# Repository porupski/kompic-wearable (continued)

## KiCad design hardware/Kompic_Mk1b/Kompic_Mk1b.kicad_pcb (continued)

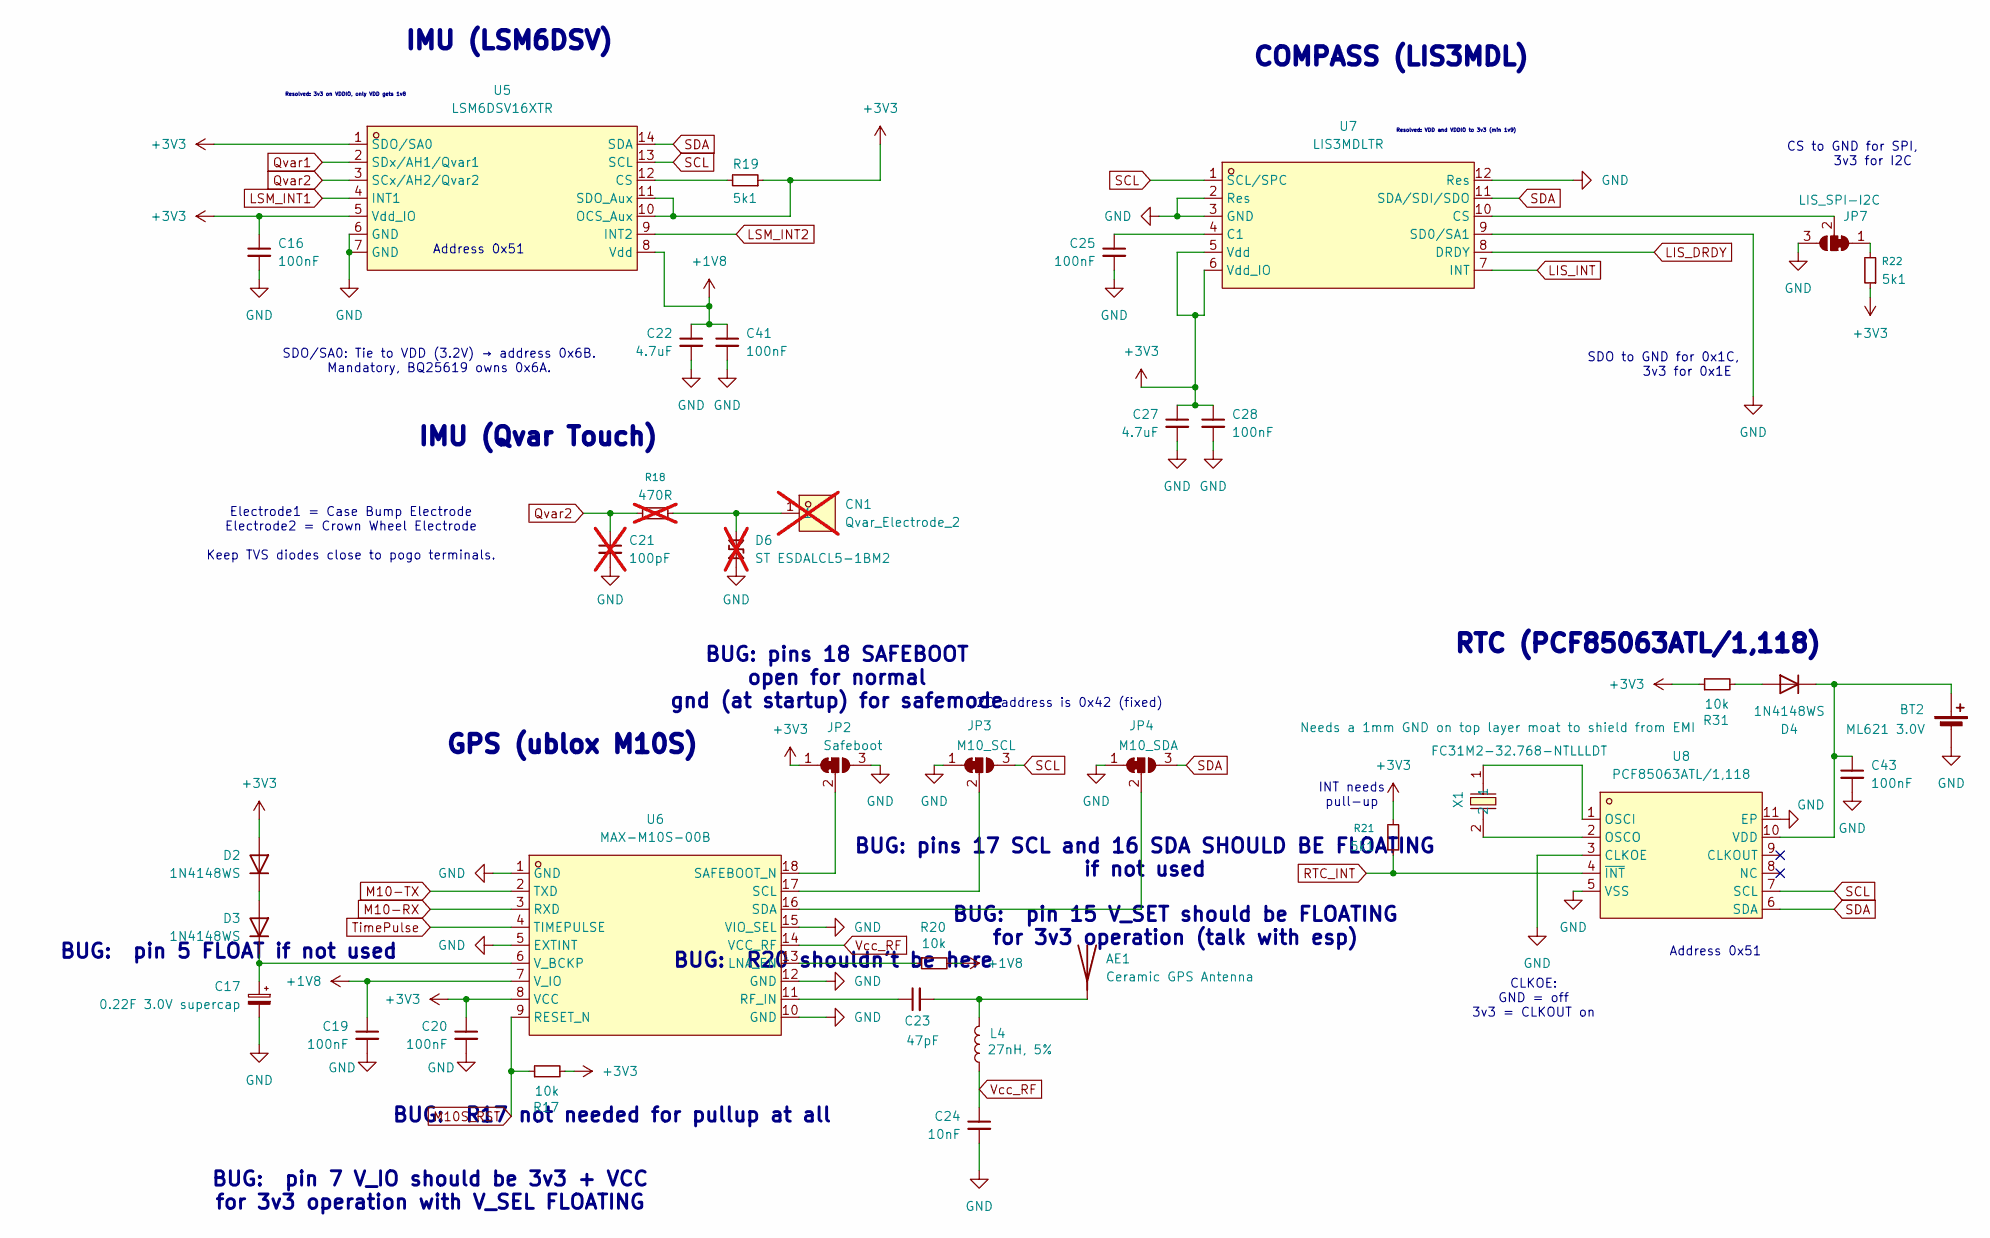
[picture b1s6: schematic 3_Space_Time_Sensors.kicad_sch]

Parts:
AE1: Ceramic GPS Antenna; GPS_Ceramic_Antenna_8x8mm_v1.0
BT2: ML621 3.0V; DMS_3R3_224_supercap_feets_v1
C16, C19, C20, C25, C28, C41, C43: 100nF; C_0402_1005Metric_Pad0.74x0.62mm_HandSolder
C17: 0.22F 3.0V supercap; DMS_3R3_224_supercap_feets_v1
C21: 100pF; C_0402_1005Metric_Pad0.74x0.62mm_HandSolder; not fitted
C22, C27: 4.7uF; C_0402_1005Metric_Pad0.74x0.62mm_HandSolder
C23: 47pF; C_0402_1005Metric_Pad0.74x0.62mm_HandSolder
C24: 10nF; C_0402_1005Metric_Pad0.74x0.62mm_HandSolder
CN1: Qvar_Electrode_2; TestPoint_Pad_D1.5mm; MPN YZR0028-15020-01; LCSC Part C7429439; not fitted
D2, D3, D4: 1N4148WS; D_SOD-323
D6: ST ESDALCL5-1BM2; D_SOD-882; not fitted
JP2: Safeboot; SolderJumper-3_P1.3mm_Bridged2Bar12_RoundedPad1.0x1.5mm
JP3: M10_SCL; SolderJumper-3_P1.3mm_Bridged2Bar12_RoundedPad1.0x1.5mm
JP4: M10_SDA; SolderJumper-3_P1.3mm_Bridged2Bar12_RoundedPad1.0x1.5mm
JP7: LIS_SPI-I2C; SolderJumper-3_P1.3mm_Bridged2Bar12_RoundedPad1.0x1.5mm
L4: 27nH, 5%; C_0402_1005Metric_Pad0.74x0.62mm_HandSolder
R17, R20, R31: 10k; R_0402_1005Metric_Pad0.72x0.64mm_HandSolder
R18: 470R; R_0402_1005Metric_Pad0.72x0.64mm_HandSolder; not fitted
R19, R21, R22: 5k1; R_0402_1005Metric_Pad0.72x0.64mm_HandSolder
U5: LSM6DSV16XTR; LGA-14_L3.0-W2.5-P0.50-BR; LCSC Part C5267406
U6: MAX-M10S-00B; SMD-18_L10.1-W9.7-P1.10-TL_SKG09F; LCSC Part C4153167
U7: LIS3MDLTR; LGA-12_L2.0-W2.0-P0.50-BL; LCSC Part C478483
U8: PCF85063ATL/1,118; DFN-10_L2.6-W2.6-P0.50-BL-EP; LCSC Part C404360
X1: FC31M2-32.768-NTLLLDT; CRYSTAL-SMD_L3.2-W1.5-1; LCSC Part C2842180

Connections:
+1V8: C19.1, C22.1, C41.1, R20.2, U5.8 (Vdd), U6.7 (V_IO); also elsewhere on the board
+3V3: C16.1, C20.1, C27.1, C28.1, D2.2 (A), JP2.1 (A), R17.2, R19.1, R21.2, R22.1, R31.1, U5.1 (SDO/SA0), U5.5 (Vdd_IO), U5.10 (OCS_Aux), U5.11 (SDO_Aux), U6.8 (VCC), U7.5 (Vdd), U7.6 (Vdd_IO); also elsewhere on the board
GND: BT2.2 (-), C16.2, C17.2, C19.2, C20.2, C21.2, C22.2, C24.2, C25.2, C27.2, C28.2, C41.2, C43.2, D6.1 (A1), JP2.3 (B), JP3.1 (A), JP4.1 (A), JP7.3 (B), U5.6 (GND), U5.7 (GND), U6.1 (GND), U6.5 (EXTINT), U6.10 (GND), U6.12 (GND), U6.15 (VIO_SEL), U7.2 (Res), U7.3 (GND), U7.9 (SD0/SA1), U7.12 (Res), U8.3 (CLKOE), U8.5 (VSS), U8.11 (EP); also elsewhere on the board
LIS_DRDY: U7.8 (DRDY); also elsewhere on the board
LIS_INT: U7.7 (INT); also elsewhere on the board
LSM_INT1: U5.4 (INT1); also elsewhere on the board
LSM_INT2: U5.9 (INT2); also elsewhere on the board
M10-RX: U6.3 (RXD); also elsewhere on the board
M10-TX: U6.2 (TXD); also elsewhere on the board
M10S_RST: R17.1, U6.9 (RESET_N); also elsewhere on the board
unnamed: AE1.1 (A_1), C23.2, L4.1
unnamed: BT2.1 (+), C43.1, D4.1 (K), U8.10 (VDD)
unnamed: D2.1 (K), D3.2 (A)
unnamed: C17.1, D3.1 (K), U6.6 (V_BCKP)
unnamed: D4.2 (A), R31.2
unnamed: CN1.1 (1_1), D6.2 (A2), R18.2
unnamed: JP2.2 (C), U6.18 (SAFEBOOT_N)
unnamed: JP3.2 (C), U6.17 (SCL)
unnamed: JP4.2 (C), U6.16 (SDA)
unnamed: JP7.1 (A), R22.2
unnamed: JP7.2 (C), U7.10 (CS)
unnamed: R19.2, U5.12 (CS)
unnamed: R20.1, U6.13 (LNA_EN)
unnamed: C23.1, U6.11 (RF_IN)
unnamed: C25.1, U7.4 (C1)
unnamed: U8.1 (OSCI), X1.1
unnamed: U8.2 (OSCO), X1.2
Qvar1: U5.2 (SDx/AH1/Qvar1); also elsewhere on the board
Qvar2: C21.1, R18.1, U5.3 (SCx/AH2/Qvar2)
RTC_INT: R21.1, U8.4 (~INT); also elsewhere on the board
SCL: JP3.3 (B), U5.13 (SCL), U7.1 (SCL/SPC), U8.7 (SCL); also elsewhere on the board
SDA: JP4.3 (B), U5.14 (SDA), U7.11 (SDA/SDI/SDO), U8.6 (SDA); also elsewhere on the board
TimePulse: U6.4 (TIMEPULSE); also elsewhere on the board
Vcc_RF: C24.1, L4.2, U6.14 (VCC_RF)

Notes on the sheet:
SDO/SA0: Tie to VDD (3.2V) → address 0x6B. Mandatory, BQ25619 owns 0x6A.
Address 0x51
COMPASS (LIS3MDL)
CLKOE: GND = off 3v3 = CLKOUT on
BUG: pin 7 V_IO should be 3v3 + VCC for 3v3 operation with V_SEL FLOATING
Electrode1 = Case Bump Electrode Electrode2 = Crown Wheel Electrode Keep TVS diodes close to pogo terminals.
BUG: R20 shouldn't be here
IMU (Qvar Touch)
BUG: pin 15 V_SET should be FLOATING for 3v3 operation (talk with esp)
INT needs pull-up
I2C address is 0x42 (fixed)
Resolved: VDD and VDDIO to 3v3 (min 1v9)
BUG: R17 not needed for pullup at all
BUG: pins 17 SCL and 16 SDA SHOULD BE FLOATING if not used
Resolved: 3v3 on VDDIO, only VDD gets 1v8
CS to GND for SPI, 3v3 for I2C
IMU (LSM6DSV)
GPS (ublox M10S)
SDO to GND for 0x1C, 3v3 for 0x1E
BUG: pin 5 FLOAT if not used
BUG: pins 18 SAFEBOOT open for normal gnd (at startup) for safemode
RTC (PCF85063ATL/1,118)

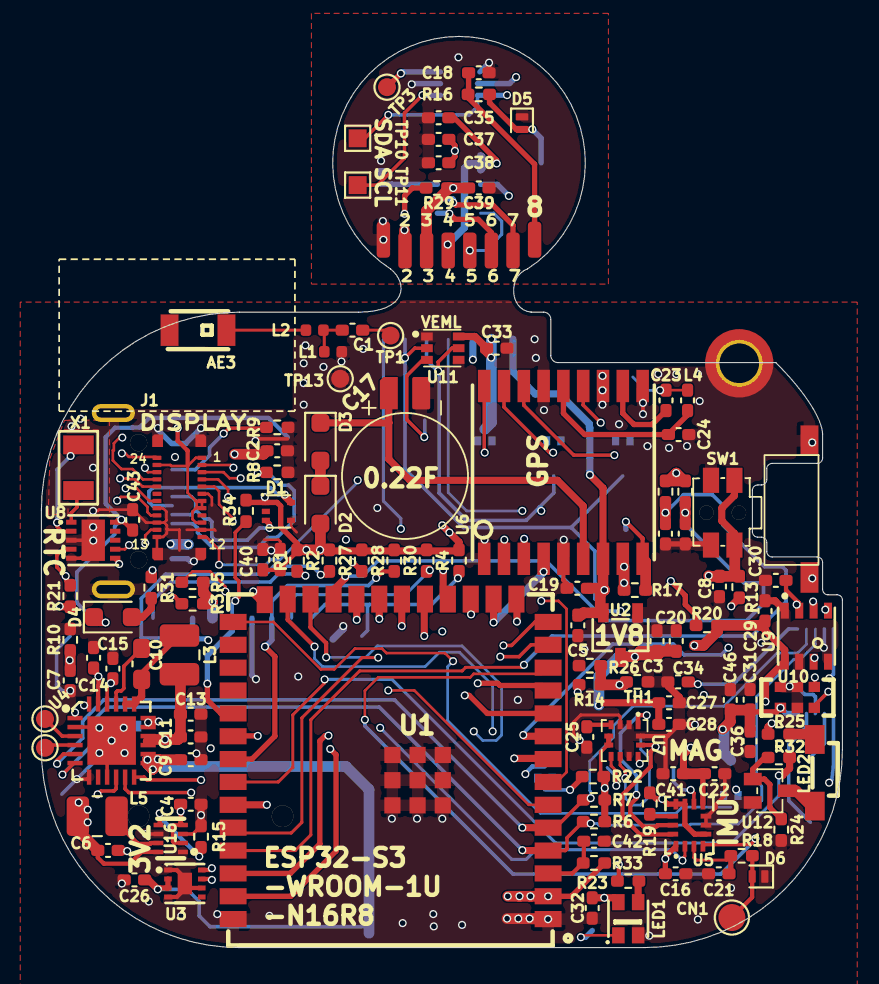
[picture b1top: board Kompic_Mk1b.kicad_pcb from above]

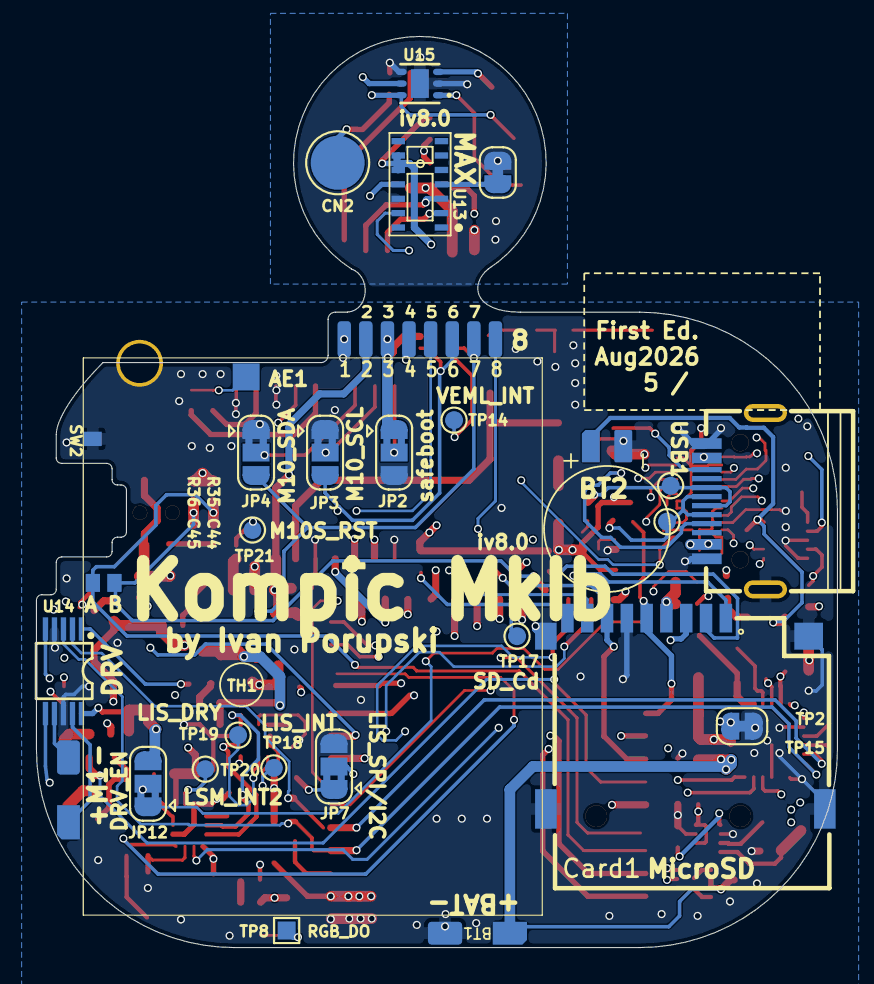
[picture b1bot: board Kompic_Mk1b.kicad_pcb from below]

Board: 4 copper layers, 44.5 x 50.6 mm, 149 parts (27 on the bottom side), 104 nets.

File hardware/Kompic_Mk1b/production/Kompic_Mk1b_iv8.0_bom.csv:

Designator,Footprint,Quantity,Value,LCSC Part #
AE1,GPS_Ceramic_Antenna_8x8mm_v1.0,1,Ceramic GPS Antenna,
AE3,ANT-SMD_L3.2-W1.6,1,2450AT18A100E,C89334
BT1,Battery_solder_terminals_v1,1,"LiPo 3,7V 380mAh",
BT2,DMS_3R3_224_supercap_feets_v1,1,ML621 3.0V,
C1,0402,1,1.0pF,
C10,0603,1,47nF,
"C11, C13, C14, C2, C3, C46, C5, C6, C9",0402,9,10uF,
"C15, C22, C27, C35, C4",0402,5,4.7uF,
"C16, C19, C20, C25, C26, C28, C29, C30, C31, C32, C33, C38, C39, C40, C41, C43, C44, C45, C8",0402,19,100nF,
C17,DMS_3R3_224_supercap_feets_v1,1,0.22F 3.0V supercap,
C23,0402,1,47pF,
C24,0402,1,10nF,
"C34, C36, C37, C42, C47, C7",0402,6,1uF,
CARD1,TF-SMD_TF-PUSH,1,TF PUSH,C393941
D1,SOT-553-5_L1.6-W1.2-P0.50-LS1.6-BR,1,TPD2E001DRLR,C150526
"D2, D3, D4",D_SOD-323,3,1N4148WS,
J1,Connector_b2b_OK-F024-04_v1,1,Conn_02x12_OK-14F024-04_v1,
J2,Custom_8_pin_for_SmartWatch_v4-MB-straightline,1,MB Interface,
J3,Custom_8_pin_for_SmartWatch_v4-DB-semicircle,1,DB-Interface,
L1,0402,1,2.7nH,
L2,0402,1,3.9nH,
"L3, L5",1008,2,2.2uH,
L4,0402,1,"27nH, 5%",
LED1,LED-SMD_4P-L2.0-W2.0-TL_WS2812B-2020,1,WS2812B-2020,C965555
LED2,LED-SMD_TJ-S4008SW4TGLCCW-A5,1,TJ-S4008SW4TGLCCW-A5,C601698
M1,Battery_solder_terminals_v1,1,ELV1411A,
"R1, R10, R13, R17, R2, R20, R24, R27, R28, R30, R31, R33, R34, R35, R36, R4",0402,16,10k,
"R14, R19, R21, R22, R29, R3, R5, R6, R7, R8, R9",0402,11,5k1,
R15,0402,1,100k,
R23,0402,1,33R,
R25,0402,1,100R,
R26,0402,1,33k,
R32,0402,1,3k3,
SW1,KEY-SMD_4P-SKSCLXX010,1,SKSCLBE010,C115361
SW2,SW-SMD_EC05E1220401-CUSTOM-ORIENT_v1,1,EC05E1220401,C116648
TH1,0402,1,NTC 10k,C77131
TP1,TestPoint_Pad_D1.0mm,1,50R BLE sig,
TP10,TestPoint_Pad_1.0x1.0mm,1,SDA,
TP11,TestPoint_Pad_1.0x1.0mm,1,SCL,
TP13,TestPoint_Pad_D1.0mm,1,50R BLE gnd,
TP14,TestPoint_Pad_D1.0mm,1,VEML_INT,
TP15,TestPoint_Pad_D1.0mm,1,BQ_STAT,
TP17,TestPoint_Pad_D1.0mm,1,SD_Cd,
TP18,TestPoint_Pad_D1.0mm,1,LIS_INT,
TP19,TestPoint_Pad_D1.0mm,1,LIS_DRDY,
TP2,TestPoint_Pad_D1.0mm,1,PMID_GOOD,
TP20,TestPoint_Pad_D1.0mm,1,LSM_INT2,
TP21,TestPoint_Pad_D1.0mm,1,M10S_RST,
TP22,TestPoint_Pad_D1.0mm,1,USB_D+,
TP23,TestPoint_Pad_D1.0mm,1,USB_D-,
TP3,TestPoint_Pad_D1.0mm,1,TMP_ALRT,
TP8,TestPoint_Pad_1.0x1.0mm,1,RGB_DO,
U1,WIRELM-SMD_ESP32-S3-WROOM-1U,1,ESP32-S3-WROOM-1U-N16R8,C3013946
U10,MIC-SMD_6P-L4.0-W2.0_LMD4020T261-OC3,1,MSM261DGT003,C48227730
U11,SENSORS-SMD_VEML6030,1,VEML6030,C132182
U12,SC-70-3_L2.0-W1.3-P0.65-LS2.1-BL,1,BSS138W_C890266,C890266
U13,OESIP-14_L5.6-W3.3-P0.80-TL,1,MAX30101EFD+T,C2859066
U14,VSSOP-10_L3.0-W3.0-P0.50-LS4.9-BL,1,DRV2605LDGSR,C527464
U15,WSON-6_L2.0-W2.0-P0.65-TL-EP,1,TMP117AIDRVR,C699536
U16,VSON-8_L2.0-W1.5-P0.50-BL,1,TPS62840DLCR,C2071859
U2,SOT-23-3_L2.9-W1.6-P1.90-LS2.8-BR,1,XC6206P182MR,C21659
U3,TDFN-8_L2.0-W2.0-P0.50-BL-EP1.2,1,MAX17048G+T10,C2682616
U4,WQFN-24_L4.0-W4.0-P0.50-TL-EP2.7,1,BQ25619RTWR,C2864534
U5,LGA-14_L3.0-W2.5-P0.50-BR,1,LSM6DSV16XTR,C5267406
U6,SMD-18_L10.1-W9.7-P1.10-TL_SKG09F,1,MAX-M10S-00B,C4153167
U7,LGA-12_L2.0-W2.0-P0.50-BL,1,LIS3MDLTR,C478483
U8,DFN-10_L2.6-W2.6-P0.50-BL-EP,1,"PCF85063ATL/1,118",C404360
U9,LGA-8_L3.0-W3.0-P0.80_BME688,1,BME688_C3664478,C3664478
USB1,USB-C-SMD_JS16T-TYPE-C479-DWH2-FSQ,1,JS16T-TYPE-C479-DWH2-FSQ,C49118447
X1,CRYSTAL-SMD_L3.2-W1.5-1,1,FC31M2-32.768-NTLLLDT,C2842180

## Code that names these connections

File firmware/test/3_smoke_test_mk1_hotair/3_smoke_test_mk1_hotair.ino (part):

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 *
 * Sequence:
 *   1. Banner, LEDC/button/encoder init, boot flash.
 *   2. Drive DRV_EN (GPIO0) HIGH so the haptic chip leaves shutdown
 *      before any bus 2 traffic. Internal boot pull-up alone does
 *      NOT hold it after the ROM bootloader releases the strap.
 *   3. Full I2C scan on both buses.
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#define PIN_BUTTON        16
#define PIN_SDA_BUS1       1    // east edge — RTC + ALS/IMU/mag/env
#define PIN_SCL_BUS1       2
#define PIN_SDA_BUS2       4    // west edge — BQ charger + DRV2605L
#define PIN_SCL_BUS2       5
#define PIN_RTC_INT       15
#define PIN_LSM_INT1       8
#define PIN_WS2812_DIN    42
#define PIN_MIC_CLK       47
#define PIN_MIC_DATA      48
#define PIN_SD_CLK        38
#define PIN_SD_CMD        39
#define PIN_SD_D0         40
#define PIN_DRV_EN         0    // strap (boot-only pull-up); FW must drive HIGH
#define PIN_ENC_A         21    // RTC wake-capable
#define PIN_ENC_B         43    // U0TXD — boot-log blip before user code runs

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
    ledcAttach(PIN_FLASHLIGHT, LED_FREQ_HZ, LED_RES_BITS);
    pinMode(PIN_BUTTON,   INPUT_PULLUP);
    pinMode(PIN_RTC_INT,  INPUT);
    pinMode(PIN_LSM_INT1, INPUT);
    pinMode(PIN_ENC_A,    INPUT_PULLUP);
    pinMode(PIN_ENC_B,    INPUT_PULLUP);
    Serial.println("[GPIO] flashlight LEDC, button, RTC-INT, LSM-INT1, EC_A/B init");

    // DRV_EN: GPIO0 strap pull-up releases after ROM. Drive HIGH explicitly so
    // the DRV2605L is awake before bus 2 probes (20.14 W-01).
    pinMode(PIN_DRV_EN, OUTPUT);
    digitalWrite(PIN_DRV_EN, HIGH);
    delay(5);   // ≥1.5 ms device-ready per datasheet
    Serial.println("[DRV ] EN driven HIGH on GPIO0");

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
    // ── I2C buses ────────────────────────────────────────────────────────────
    Serial.printf("[I2C ] Bus1 SDA=%d SCL=%d  Bus2 SDA=%d SCL=%d  @ 400 kHz\n",
                  PIN_SDA_BUS1, PIN_SCL_BUS1, PIN_SDA_BUS2, PIN_SCL_BUS2);
    Wire.begin(PIN_SDA_BUS1, PIN_SCL_BUS1, 400000);
    Wire1.begin(PIN_SDA_BUS2, PIN_SCL_BUS2, 400000);
    delay(20);

    Serial.println();
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
    // ── PDM mic ──────────────────────────────────────────────────────────────
    Serial.printf("[MIC ] PDM init: CLK=GPIO%d DATA=GPIO%d  %u Hz / 16-bit / mono\n",
                  PIN_MIC_CLK, PIN_MIC_DATA, (unsigned)MIC_SAMPLE_RATE_HZ);
    i2s_mic.setPinsPdmRx(PIN_MIC_CLK, PIN_MIC_DATA);
    if (i2s_mic.begin(I2S_MODE_PDM_RX, MIC_SAMPLE_RATE_HZ,
                      I2S_DATA_BIT_WIDTH_16BIT, I2S_SLOT_MODE_MONO)) {
        i2s_mic.setTimeout(100);
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    // 10 kΩ to 3V2. 400 kHz is the SD identification clock; anything faster
    // previously failed signal integrity past CMD9 / ACMD51 / ACMD41.
    Serial.printf("[SD  ] SDMMC 1-bit init: CLK=GPIO%d CMD=GPIO%d D0=GPIO%d  @ 400 kHz\n",
                  PIN_SD_CLK, PIN_SD_CMD, PIN_SD_D0);
    if (!SD_MMC.setPins(PIN_SD_CLK, PIN_SD_CMD, PIN_SD_D0)) {
        Serial.println("       setPins FAILED -- pin config rejected by SD_MMC");
    } else if (!SD_MMC.begin("/sdcard", true /*mode1bit*/, false /*format_if_fail*/,
                             400 /*sdmmc_frequency, kHz*/)) {
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
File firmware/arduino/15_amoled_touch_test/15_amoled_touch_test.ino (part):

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 * standalone breakout — pins re-aligned to the iv7.1 master pinout v20.
 *
 * ── Pin changes vs the old breakout sketch ──────────────────────────
 *   TOUCH_RST : 5  -> 44   (GPIO5 is now SCL_bus2 for the BQ25619)
 *   QSPI_TE   : 21 -> 45   (unused in this sketch either way)
 *   Everything else (QSPI 9..14, CS=10, DISP_RST=3, TOUCH_SDA=1/SCL=2/INT=6)
 *   matches — those pins were already correct.
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//  PINS — iv7.1 master pinout v20
// ════════════════════════════════════════════════════════════════════

#define QSPI_CS     10
#define QSPI_CLK    12
#define QSPI_D0     11   // MOSI  (SIO0)
#define QSPI_D1     13   // MISO  (SIO1)
#define QSPI_D2      9   // WP    (SIO2)
#define QSPI_D3     14   // HD    (SIO3)
#define DISP_RST     3   // JTAG-src strap; safe on iv7.1 per master pinout
// #define QSPI_TE   45   // TE routed on iv7.1 but not used in this sketch

#define TOUCH_SDA    1   // bus 1 (shared with LSM, TMP117, MAX30101, RTC, ...)
#define TOUCH_SCL    2
#define TOUCH_INT    6
#define TOUCH_RST   44   // was 5 on the breakout; 5 is now SCL_bus2
#define TOUCH_ADDR  0x5A

#define BUTTON_PIN  16   // BQ_BUTTON, doubles as BQ /QON
#define SDA_BUS2     4   // BQ25619 lives here
#define SCL_BUS2     5
#define BQ_ADDR     0x6A

// ── BQ25619 ship-mode registers (same as 4_demo_mk1 / 12_lsm_full) ──
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// ════════════════════════════════════════════════════════════════════

static void spi_init() {
  pinMode(QSPI_CS, OUTPUT);
  CS_HIGH();

  spi_bus_config_t bus = {};
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
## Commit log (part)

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2026-05-30 First index page and licences added.
2026-05-30 Update README.md with page link
2026-05-30 Updated Index page with placeholder images. Added Licences to respective folders.
2026-05-30 Big Kompic Mk1 release! First KiCad 10 SCH and PCB files available. Including production files, information about parts and placement, as well as a Reflow guide.
2026-06-01 BIG CHANGE: Had bad wiring for the AMOLED, had to redo the schematic and complete routing of PCB (iv7.1). Added Arduino sketch for verifying AMOLED. Added newly redone pinout for both ESP32-S3 and th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
2026-06-01 Fabrication page live! Updated all KiCad 10 files to final form. First fabrication+aseembly is on the way!
2026-06-02 Added Circuit page! Minor touchups to schematic + Schematic PDF.
2026-06-03 Added Circuit page!
2026-06-03 Fixed ML651 -> ML621 battery name.
2026-06-10 [CO5300] Porting: AMOLED display driver, iv7.2.f0.0, 5 issues noted
    - Hardware spec extracted from v7.2 (DISPLAY section + GPIO quick pinout)
    - Driver skeleton: full register map, SPI framing for both 0x02 (1-wire
    instruction) and 0x32 (QIO pixel) paths, init sequence, sleep/wake.
    - Test harness: chip identity, init, status read, DISPON, brightness 50/100,
    sleep/wake, single-pixel QIO push, heap accounting, all timed via
    esp_timer_get_time().
2026-06-10 Added the docs folder, contaning all master prompt, system instructions, project blueprints and individual model phase prompts for porting semi-working firmware code from prototype II. Currently buil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
2026-06-10 updated .gitignore
2026-06-12 [SDCard] Porting: SDMMC 1-bit + FatFS storage, iv7.2.f0.0, 7 issues noted
    - New components/sdcard/ component (no v5 carryforward). SDMMC host
    on GPIO38/39/40 (CLK/CMD/DAT0). 1-bit mode -- DAT1-3 unrouted
    per v7.2. FatFS mount at /sd, 16 KiB allocation unit.
    - On-demand mount: sdcard_init() does only the mutex; sdcard_mount()
    spins the host. sdcard_unmount() parks the host between sessions
    for the power budget.
2026-06-12 [PDM_Mic] Porting: I2S0 PDM RX audio capture, iv7.2.f0.0, 6 issues noted
    - New components/mic_pdm/ component (no v5 carryforward). IDF v5
    i2s_pdm RX channel on I2S0; CLK=GPIO47, DIN=GPIO48 per v7.2.
    - Capture: 16 kHz, 16-bit signed, mono, LEFT slot (matches JP9=GND
    per v7.2 §SOLDER JUMPERS). 20 ms frame = 320 samples = 640 bytes.
    6 DMA frames in PSRAM = 120 ms total buffer.
    - API: _init / _deinit / _start / _stop / _is_running / _read /
2026-06-12 [QvarECG] Porting: LSM6DSV16X Qvar ECG channel, iv7.2.f0.0, 7 issues noted
    - New components/qvar_ecg/ component (no v5 carryforward).
    Single-lead ECG via the LSM6DSV16X embedded Analog-Hub / Qvar
    channel. Shares I2C bus 1 + g_i2c_mutex with the IMU driver.
    - Enables CTRL7.AH_QVAR_EN + selects ZIN=235 MOhm (lowest impedance,
    best for pogo-pin skin contact). Read-before-write preserves any
    bits the IMU driver may have set in CTRL7 (Blueprint 4 §3).
2026-06-13 test signed commit
2026-06-13 Slight wording change.
2026-06-13 [DataBroker] Porting: v7.2 chip headers + TMP117 skin slot, iv7.2.f0.0, 3 issues noted - Swapped 7 chip headers: tu10f→max_m10s, qmc5883p→lis3mdl, app_battery→bq25619, bh1750→veml6030, qmi8658→lsm6ds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
2026-06-13 [CrossDriver] Porting: v7.2 event catalogue, iv7.2.f0.0, 2 issues noted - Refreshed three chip-name comments (BME688/MAX30101/VEML6030). - Appended seven new event ordinals at the tail of the enum: S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
2026-06-13 [AppNVS] Porting: drop app_battery, drop esp_adc, iv7.2.f0.0, 2 issues noted - CMakeLists: dropped app_battery.c from SRCS (file gone) and dropped driver + esp_adc from REQUIRES (BQ25619 reads batter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
2026-06-13 [Fusion] Porting: BME688 baro altitude wired, iv7.2.f0.0, 2 issues noted - Activated the BME688 read path in task_fusion_fn — broker now exposes broker_env_read, the v5 stub block can land. - Removed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
2026-06-13 [Alarm] Porting: buzzer field → WS2812 LED strobe, iv7.2.f0.0, 3 issues noted - Renamed alarm_slot_t.buzzer → led_strobe. v7.2 GPIO42 is the WS2812 status LED (no piezo as in v5). NVS key "buzz" pres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
2026-06-13 [LvglUI] Porting: v7.2 tile registry + ECG stub tile, iv7.2.f0.0, 3 issues noted - tile_registry.c: header comment retargeted to the v7.2 part list (LIS3MDLTR, LSM6DSV16X, VEML6030, MAX-M10S, BME688,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
2026-06-13 [Phase6] Add trailing v7.2-compatible files missed in module commits The six Phase 6 module commits staged only files I had edited. These 29 remaining files are unchanged-from-v5-cp content that's al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
2026-06-13 [Build] Firmware scaffolding — project root, main task, partition table - firmware/CMakeLists.txt — top-level ESP-IDF project, name = smartwatch. - firmware/main/CMakeLists.txt + main.c + idf_compone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
2026-06-13 Added the remaining files. datasheet_manifest.md contains info and links to all datasheets of the components. 06 reports an Opus simulation of the system, trying to find bottlenecks in the hardware. 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
2026-06-13 Slight edits in numbering.
2026-06-13 I was under the impression it was iv7.2, while it is in fact iv7.1, causing a "cosmetic" mass-revision. I am but a single man flooring some silicon.
2026-06-13 Slowly but surely.
2026-06-14 [Docs] Phase 1 datasheet extracts (20.01–20.05) — Display + Touch + Core Five chip extracts complete: CO5300 AMOLED, CST9217 touch, ESP32-S3 MCU, PCF85063A RTC, TPS62840 buck. Each file follows the m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
2026-06-18 [Docs] Phase 2 datasheet extracts (20.06-20.10) — Sensors Bus 1 Part A Five chip extracts complete (VEML6030, LIS3MDLTR, MAX-M10S, TMP117, LSM6DSV16X) plus a companion file (20.10b) covering the LSM6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
2026-06-18 Phase 3 datasheet extraction wrap-up.
2026-06-18 Phase 4 Datasheet extraction done.
2026-06-18 Succesful first test of partial Kompic Mk1! Reflow stage 1 includes ESP32, TPS, BQ, button and flashlight LED - all confirmed working!
2026-06-18 Reflow soldering guide: now in raw tex + profile generator script. To be updated.
2026-06-18 Final phase 5 datasheet extraction done! 20.21 Checklist for final summary.
2026-06-21 MASSIVE UPDATE: Built a working prototype with most systems go! iv7.1 requires about half a dozen surgical hacks on the PCB itself - it is suggested you wait for iv7.2+ - but otherwise, a massive suc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
    Stage 1-3 documents how the parts were added, in what fashion and then tested both electrically and with the scripts in test/ for each stage. SD Card may be unfixable in iv7.1.
    Added notes where the bugs are in the schematic, but haven't updated it.
2026-06-30 Folder maintenance.
2026-06-30 Pondering microSD card situation. Refined Encoder action in 5_smoke_test! Verifying if DRV or LRA are good. Preparing for future steps at the bench.
